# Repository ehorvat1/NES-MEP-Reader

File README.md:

# NES-MEP-Reader
Now based on amsreader-firmware Rev, 2.2.17. (from 5th Mai 2023)

So it features: WebUI with new design. WebUI componenst are now selectable in config page. WebUI works also offline (in AP mode) now. Fixed cost / kWh .Last Month info. 

From my side:
- Rel. 2.2: Fallback to Wifi AP can make AP button obsolete. 1hour plot. Additional Meter Info on status page.
- Rel. 2.3: Data fetch from meter and Web Interface now on 2 second base. New 5 minute plot.
- Rel. 2.4: Frequency Indicator, Power Factors and Reactive Data including their MQTT Topics (for Raw MQTT and HomeAssistant)
- Rel. 2.5: Added a fixed price per kWh for export.
            User can enter now a "last" counter value and a text comment for this value - idea is to enter here the last kWh from the last energy bill. A price is calculated from this "last" counter to the actual kWh counter to get an idea of costs since last energy bill. More info on minute & hour plot. Version is shown now in Status page.
- Rel. 2.6: MQTT works now for "HomeAssistant" payload. Only check for 25 Data points from BT28 (was 54)
- **current repo. state: pre 2.7: Fix table read BT23 for Gen4 meters....thanks to makerspace-reinach.ch .**
  
  **Fixed clearing of MEP error indication in header line. Fixed communication recovery and debug message if zero bytes are received.**
  
  **12 Aprl 2024, Fixed reading from table BT23 resulting in wrong "Export Reactive Arh L1L2L3"....thanks to Hubert**

  **24 Mai 2024, Only as compiled firmware in ESP32-binaries section: A version on "steroids" reading MEP port every second. Short tests did show no problems, but (as for whole project): use at own risk**

**Please Note: For MQTT I could only test payloads "raw (2 Sek.)", "raw (10 Sek.)" and "HomeAssistant" .**

This code is designed to decode data from NES (Networked Energy Services) electric smart meters which are installed in some countries in Europe (eg. Denmark and Austria, Switzerland).  
The data is presented in a graphical web interface and can also send the data to a MQTT broker which makes it suitable for home automation project.

This project is basically merging 2 other project into one:
1) amsreader-firmware (old name: AmsToMqttBridge) Rev, 2.2.17  which can found here: https://github.com/UtilitechAS/amsreader-firmware  and
2) OSGP Alliance Documentation for MEP (Multipurpose Expansion Ports) at https://github.com/OSGP-Alliance-MEP-and-Optical and the coding work from Graves Kilsgaard and Gert Lynge from www.dabbler.dk, in combination with help from NES and OSGP Alliance. See also : https://github.com/DabblerDK/MEP-SW-ESP32 

The data from NES (Echelon) smart meters is derived using the smart meters MEP (Multipurpose Expansion Port) which is using a bi-directional serial communication link. The communication is individually secured by a secret key called "MEP Basic Key" which the relevant electrical supply company (the one which own the smart meters) has to release to the customer. (In Austria this is supported by law.)

## Quick start:
1) Flash the ESP32 using files in [ESP32-binaries](https://github.com/ehorvat1/NES-MEP-Reader/tree/main/ESP32-binaries) folder and according instructions of its readme.md file. Later subsequent firmware changes can be done via Web interface by uploading a single firmware file. (Or by connecting ESP32 to a serial port which can also upload firmware.)
2) Connect to ESP32 "AP" WIFI web page. Initially the ESP32 starts in AP mode (= presenting an WIFI Access point named stromzaehler-abcd"). Connect your Laptop/Tablet to this Wifi network using **password: nesmep_esp32#V20** and open ESP32 web page which is by default on IP: 192.168.4.1

The AP SSID and password are also shown on serial connected terminal right after booting ESP32.

3) Press "NEXT" button on initial web page, and then on next page enter your Wifi SSID, credentials and optionally a hostname. Save&Reboot.
4) Connect to ESP32 web page.
ESP32 should have connected to your Wifi and should be accessable by IP but also via its Hostname (Check out your Wifi router setup page for IP address.)
5) Configuation. Open the Configuration web page (gear icon in header). Enter data to: "Price region, currency, fixed price. Set Power saving to Off, unceck Multipliers. Set up User interface to your needs.
6) Still on Configuration page: Make sure that "Meter is encrypted" checkbox is selected. Then enter the MEP Basic key in hex format. It should look similar like this: 58747A3B7E2C685656794F45404B79724F69562B .Enter/paste the 40 character long MEP basic key into the field below. You you have to get the MBK from your local energy supplyer first. Best practice is to copy/paste from an editor. After pasting the 40 char long hex key 2 trailing zeros are shown....thats fine.
7) Still on Configuration page: Set values to fields AP button = 26 (for IO26 the GPIO pin where the AP button is connected to be able to reset ESP32 to initial AP mode)."LED" = 2 (works for my ESP32 Wemos D1 Module). 
Attention: 26 is now the default which is used after each boot of ESP32. 
The serial port connection to the MEP port is fixed in the code to UART2 which is using IO16 & IO17. RTS (Request to send) is coded to IO05.
8) For MQTT setup: Enter a MQTTs broker IP into field "Host", a unique name to "Client ID" (unique for the MQTT broker) e.g. SM1 and enter a MQTT topic into "Publish topic" field. This will be the base topic name. e.g. smartmeter.
9) 

## Wifi function (STA mode or AP mode):
The option on configuration page in section Wifi called:  "Start a Wifi AP on home Wifi connection problem" will enable this:
If the configured Wifi (should be your home Wifi) can not be reached within app. 2 minutes the ESP32 will swap to Wifi AP mode and will present a AP named "Stromzaehler-abcd" with password mentioned in above pt. 2. 

Software will try to re-connect to the configured Wifi if no client is connected to this AP for 90 seconds. So if one is connected to AP Wifi the device will stay in AP mode. Please mind that most devices will do a automatic reconnect to the AP Wifi if the Wifi connection "Stromzaehler-abcd" was once used. This could prevent the ESP32 from automatically reconnecting to defined STA Wifi.

"AP" button still is an option to swap between configured WLAN and an Wifi Access point called "Stromzaehler-abcd". The AP button must be pressed longer than 5 seconds to swap Wifi mode.

## Hardware:
For hardware please check repository [Hardware](https://github.com/ehorvat1/NES-MEP-Reader/tree/main/Hardware) and also the development done by Dabbler group at www.dabbler.dk

## Notes:
1) This was tested only on NES Smart Meters Type: 83332-3I and 83334-3I 
2) There might be problems with power supply from NES Smart meter. It seems that some meters do not supply sufficient power to ESP32. As a result you might see frequent crashes or the serial communication to MEP port not working at all. If this happens remove the DCDC converter (!) and power the ESP32 module directly from USB.
3) NES (Networked Energy Services) smart meters were previously manufactured and sold with the "Echelon" brand name.
4) Currently only ESP32 is supported although you may find remainders of ESP8266 in the code. (Yes I want to make it ESP8266 compatible....)
5) MBK (MEP Basic Key) must be entered in its "hex" representation. This is a 40 char long string like this: 58747A3B7E2C685656794F45404B79724F69562B . You might receive a MEP Basic key in ascii format (just 20 char.) which has to be converted to hex manually - each single ASCII character gives a 2 digit hex number.
6) I have done some translations to German on the main web interface. A english version will follow.
7) Following raw MQTT topics should work in MQTT raw mode - they are published on a pure time basis even if they do not change the value.:
     - Publish topic + "/meter/mep_data_ready"
     - Publish topic + "/meter/mep_alivecounter"
     - Publish topic + "/meter/manufacturer"
     - Publish topic + "/meter/model"
     - Publish topic + "/meter/serialnumber"
     - Publish topic + "/meter/firmwareversion"
     - Publish topic + "/meter/hardwareversion"
     - Publish topic + "/meter/clock"
     - Publish topic + "/meter/import/active"
     - Publish topic + "/meter/import/active/accumulated"
     - Publish topic + "/meter/export/active"
     - Publish topic + "/meter/export/active/accumulated"
     - Publish topic + "/meter/import/reactive"
     - Publish topic + "/meter/export/reactive"     
     - Publish topic + "/meter/import/reactive/accumulated"
     - Publish topic + "/meter/export/reactive/accumulated"
     - Publish topic + "/meter/l1/voltage"
     - Publish topic + "/meter/l2/voltage"
     - Publish topic + "/meter/l3/voltage"
     - Publish topic + "/meter/l1/current"
     - Publish topic + "/meter/l2/current"
     - Publish topic + "/meter/l3/current"
     - Publish topic + "/meter/l1/powerfactor"
     - Publish topic + "/meter/l2/powerfactor"
     - Publish topic + "/meter/l3/powerfactor"
     - Publish topic + "/meter/appowerVA"
     - Publish topic + "/meter/frequency"
     - Publish topic + "/meter/reactivepower_Q1"
     - Publish topic + "/meter/reactivepower_Q2"
     - Publish topic + "/meter/reactivepower_Q3"
     - Publish topic + "/meter/reactivepower_Q4"
     - Publish topic + "/realtime/import/hour"
     - Publish topic + "/realtime/import/day"
     - Publish topic + "/realtime/import/month"
     - Publish topic + "/realtime/export/hour"
     - Publish topic + "/realtime/export/day"
     - Publish topic + "/realtime/export/month"
     - Publish topic + "/realtime/import/cost_kwh"
	 
     - Publish topic + "/realtime/import/last_counter_value"
     - Publish topic + "/realtime/import/last_counter_info"
     - Publish topic + "/realtime/import/last_counter_diff"
     - Publish topic + "/realtime/import/last_counter_costs"
     - Publish topic + "/realtime/export/refund_kwh"
     - Publish topic + "/realtime/export/last_counter_value"
     - Publish topic + "/realtime/export/last_counter_info"
     - Publish topic + "/realtime/export/last_counter_diff"
     - Publish topic + "/realtime/export/last_counter_refund"

So for example, if you set the "Publish topic" in MQTT configuration to "smartmeter" the actual power used is published with full topic: smartmeter/meter/import/active   (Topics are case sensitive !)

8) MQTT for HomeAssistant: HA creates/discovers nummerical data as "Sensors". Exceptions is String data which has to be extracted from JSON data manually.

## Web interface:
The web interface is very similar to original "amsreader-firmware". I have added a 60 Minute plot, and translated to German language.
The help icons on the configuration page are linked to original "amsreader-firmware" site. Serial Port and RTS Pin are described also on config page.

## Building this project with PlatformIO
To build this project, you need [PlatformIO](https://platformio.org/) installed.

It is recommended to use Visual Studio Code with the PlatformIO plugin for development.

[Visual Studio Code](https://code.visualstudio.com/download)

[PlatformIO vscode plugin](https://platformio.org/install/ide?install=vscode)

For development purposes, copy the ```platformio-user.ini-example``` to ```platformio-user.ini``` and customize to your preference. The code will adapt to the platform and board set in your profile.

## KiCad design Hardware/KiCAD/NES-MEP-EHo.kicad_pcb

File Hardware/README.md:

# Hardware 
Updated Rev2 uploaded 21.Dec 2022

## Used parts:
1) A DC/DC step down converter set to 3.3 Volt (source: https://www.az-delivery.de/en/collections/stromversorgung/products/lm2596s-dc-dc-step-down-modul-1 )
2) A ESP32 D1 Mini Module (source: https://www.az-delivery.de/en/collections/esp32/products/esp32-d1-mini)
3) A "selfmade" printed cirquit board based on attached KICAD project. [Schema in pdf format](https://github.com/ehorvat1/NES-MEP-Reader/blob/main/Hardware/NES-MEP-EHo-shema-Rev2.pdf)

### Issues:
There might be problems with power supply from NES Smart meter. It seems that some meters do not supply sufficient power to ESP32. Or the MAX3232 charge pumps interfering with the step down converter. As a result you might see frequent crashes or the serial communication to MEP port not working. You might also notice that the MAX3232 and the step down converter getting quite warm. 
If this happens try:
1) Try with a (oversized) 470uF or 1000uF capacitor on the +3.3V and GND. This helped a lot, but still 2 or 3 tries to connect may be needed.
2) Always helps: Remove the DCDC converter (!) and power the ESP32 module directly from USB.

### Notes:
1) I have used a small "connector" board to connect to the MEP port and a flat ribbon cable. In this way the signals are transported outside of the meter. The flat ribbon cable fits through the open gap where the meter is mounted into the electric cabinet. This all is done because here in my place the MEP port is not accesable, it is covered by a plastic cover which is sealed off by the power supply company. Check out a photo of the cable and small connector card here: https://github.com/ehorvat1/NES-MEP-Reader/blob/main/Hardware/Pictures-Rev1/Assembly.JPG
2) The spacing of the MEP port terminals is different between NES smart meter models. Therefore just 5 short wires are connected to the "connector" board.

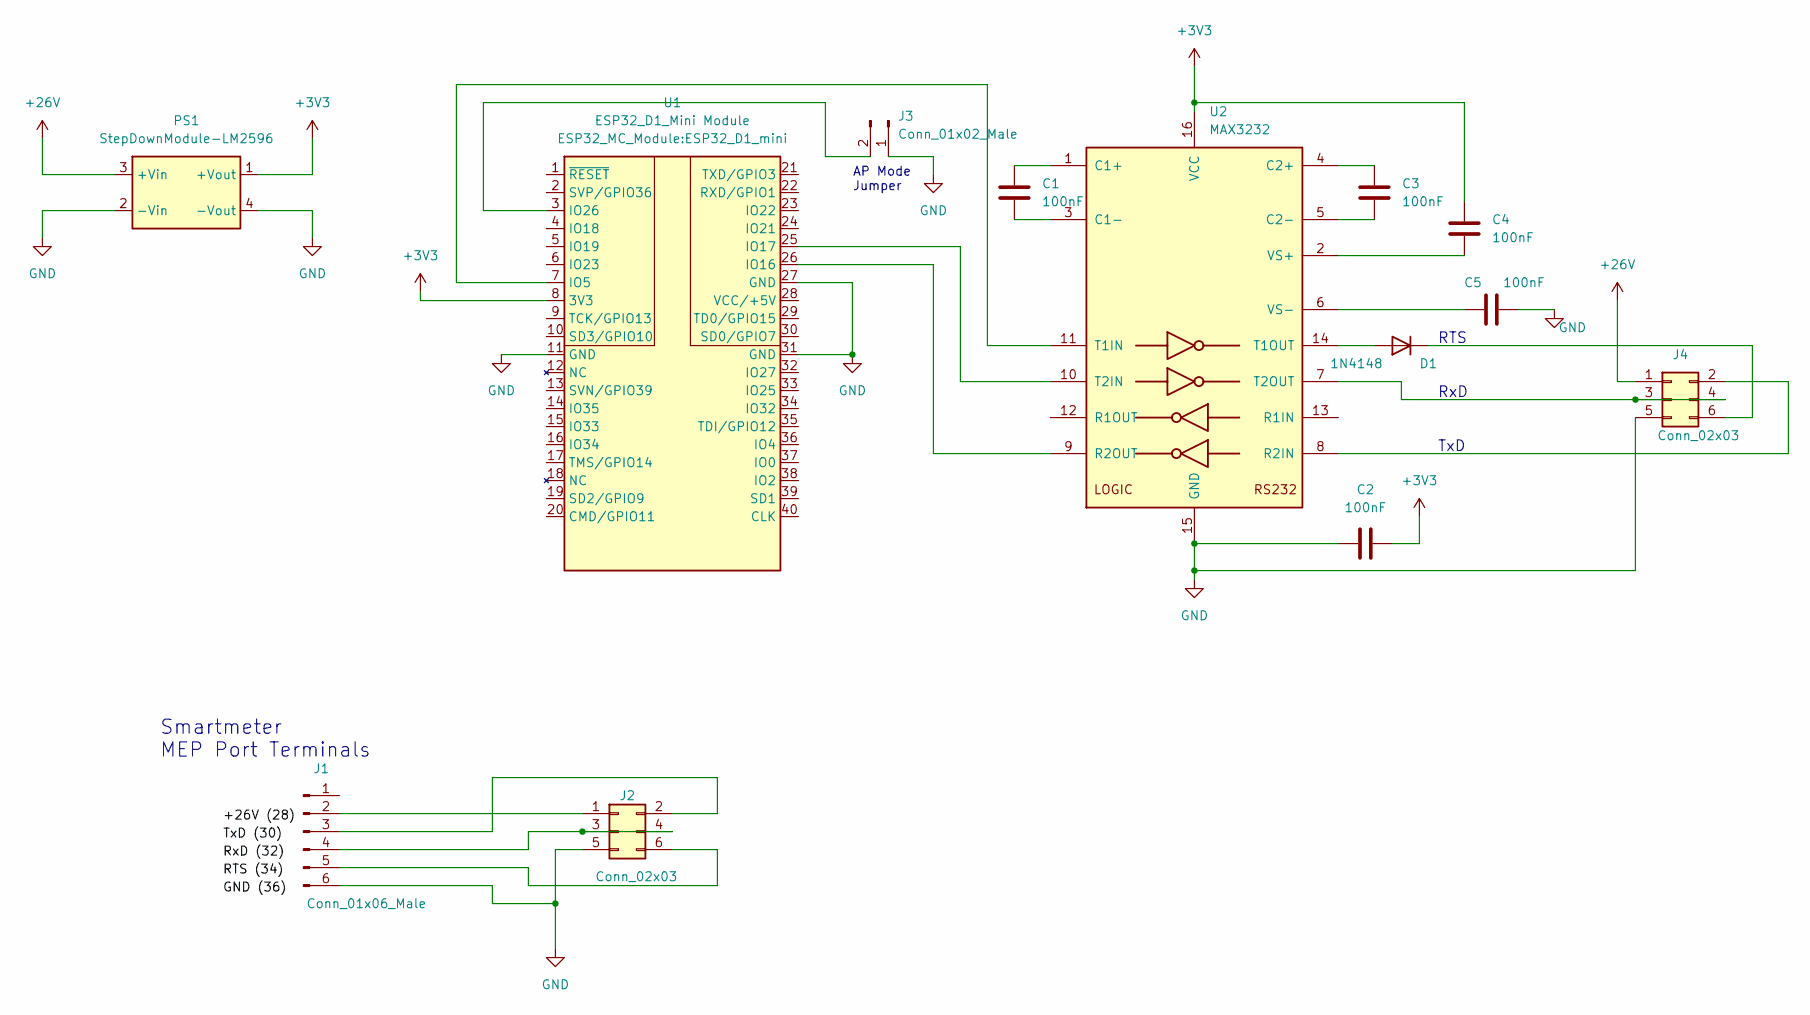
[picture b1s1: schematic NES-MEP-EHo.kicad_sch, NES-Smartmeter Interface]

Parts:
C1, C2, C3, C4, C5: 100nF; C_Rect_L7.0mm_W3.5mm_P5.00mm
D1: 1N4148; D_DO-35_SOD27_P7.62mm_Horizontal
J1: Conn_01x06_Male; SolderWire-1sqmm_1x06_P5.4mm_D1.4mm_OD2.7mm
J2, J4: Conn_02x03; IDC-Header_2x03_P2.54mm_Vertical
J3: Conn_01x02_Male; PinHeader_1x02_P2.54mm_Vertical
PS1: StepDownModule-LM2596; DCDC-StepDown-LM2596-THT
U1: ESP32_D1_Mini Module; ESP32_D1_mini
U2: MAX3232; DIP-16_W7.62mm_Socket

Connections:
+3V3: C2.2, C4.1, PS1.1 (+Vout), U1.8 (3V3), U2.16 (VCC)
+26V: J4.1, PS1.3 (+Vin)
GND: C2.1, C5.1, J1.6, J2.5, J3.1, J4.5, PS1.2 (-Vin), PS1.4 (-Vout), U1.11 (GND), U1.27 (GND), U1.31 (GND), U2.15 (GND)
unnamed: C1.1, U2.1 (C1+)
unnamed: C1.2, U2.3 (C1-)
unnamed: C3.1, U2.4 (C2+)
unnamed: C3.2, U2.5 (C2-)
unnamed: C4.2, U2.2 (VS+)
unnamed: C5.2, U2.6 (VS-)
unnamed: D1.1 (K), J4.6
unnamed: D1.2 (A), U2.14 (T1OUT)
unnamed: J1.2, J2.1
unnamed: J1.3, J2.2
unnamed: J1.4, J2.3, J2.4
unnamed: J1.5, J2.6
unnamed: J3.2, U1.3 (IO26)
unnamed: J4.2, U2.8 (R2IN)
unnamed: J4.3, J4.4, U2.7 (T2OUT)
unnamed: U1.7 (IO5), U2.11 (T1IN)
unnamed: U1.25 (IO17), U2.10 (T2IN)
unnamed: U1.26 (IO16), U2.9 (R2OUT)

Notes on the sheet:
RTS
TxD
Smartmeter MEP Port Terminals
AP Mode Jumper
RxD

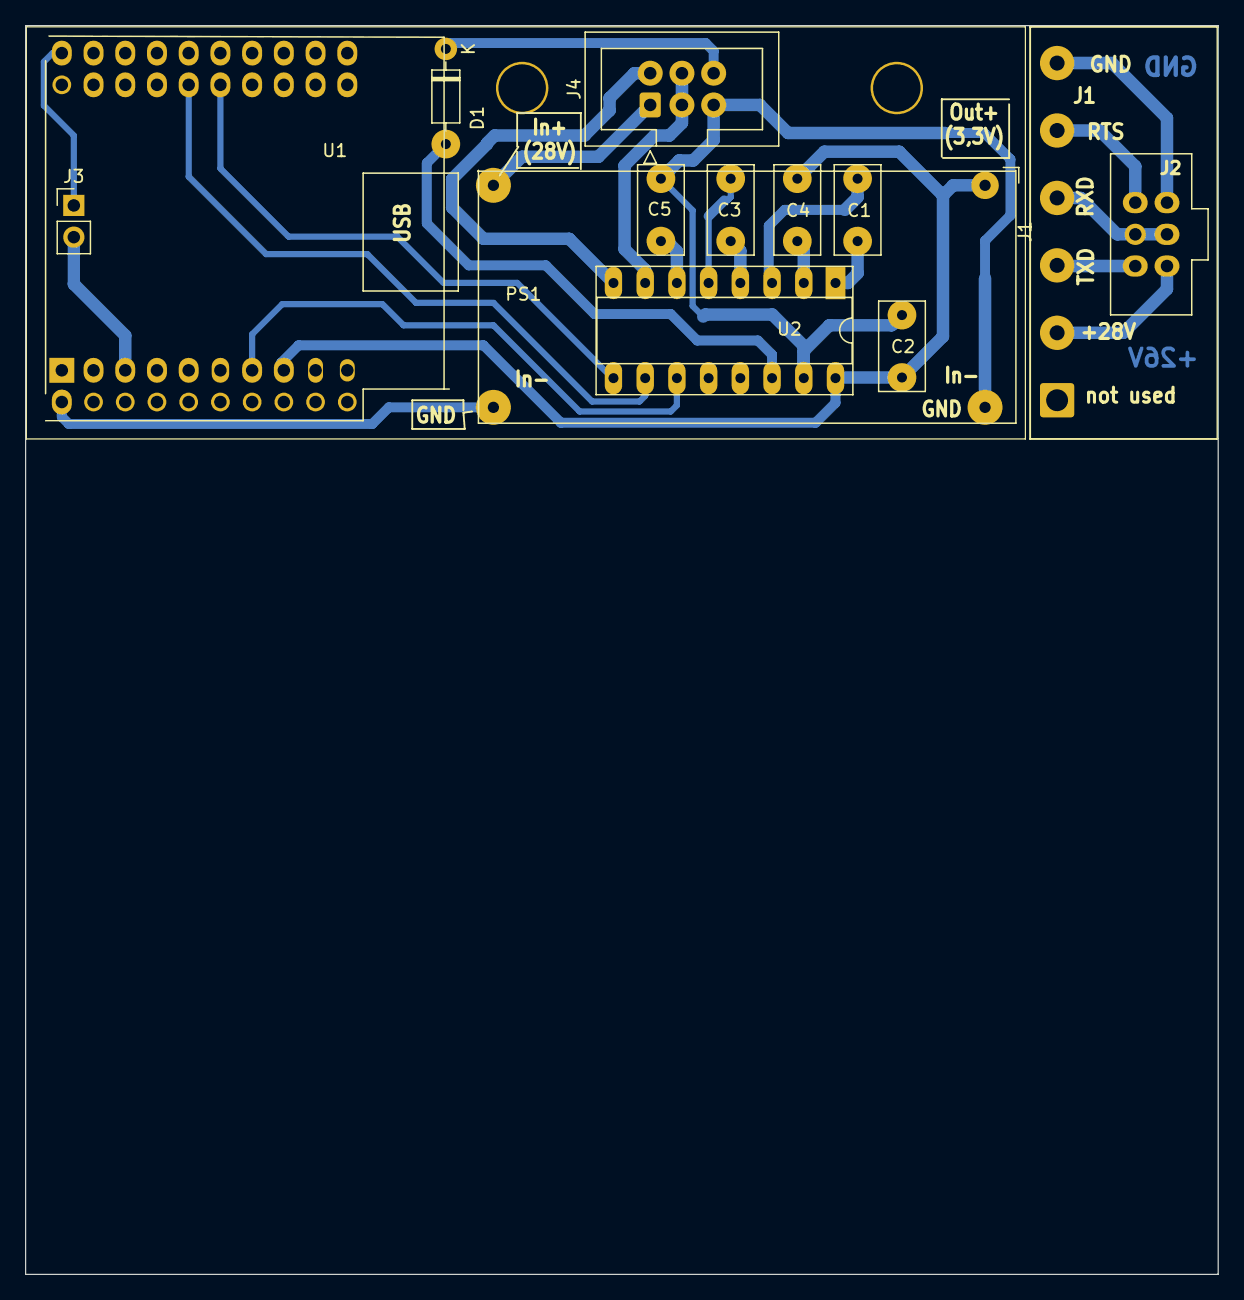
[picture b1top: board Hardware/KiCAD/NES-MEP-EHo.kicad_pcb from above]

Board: 2 copper layers, 95.5 x 100.0 mm, 13 parts (0 on the bottom side), 21 nets.

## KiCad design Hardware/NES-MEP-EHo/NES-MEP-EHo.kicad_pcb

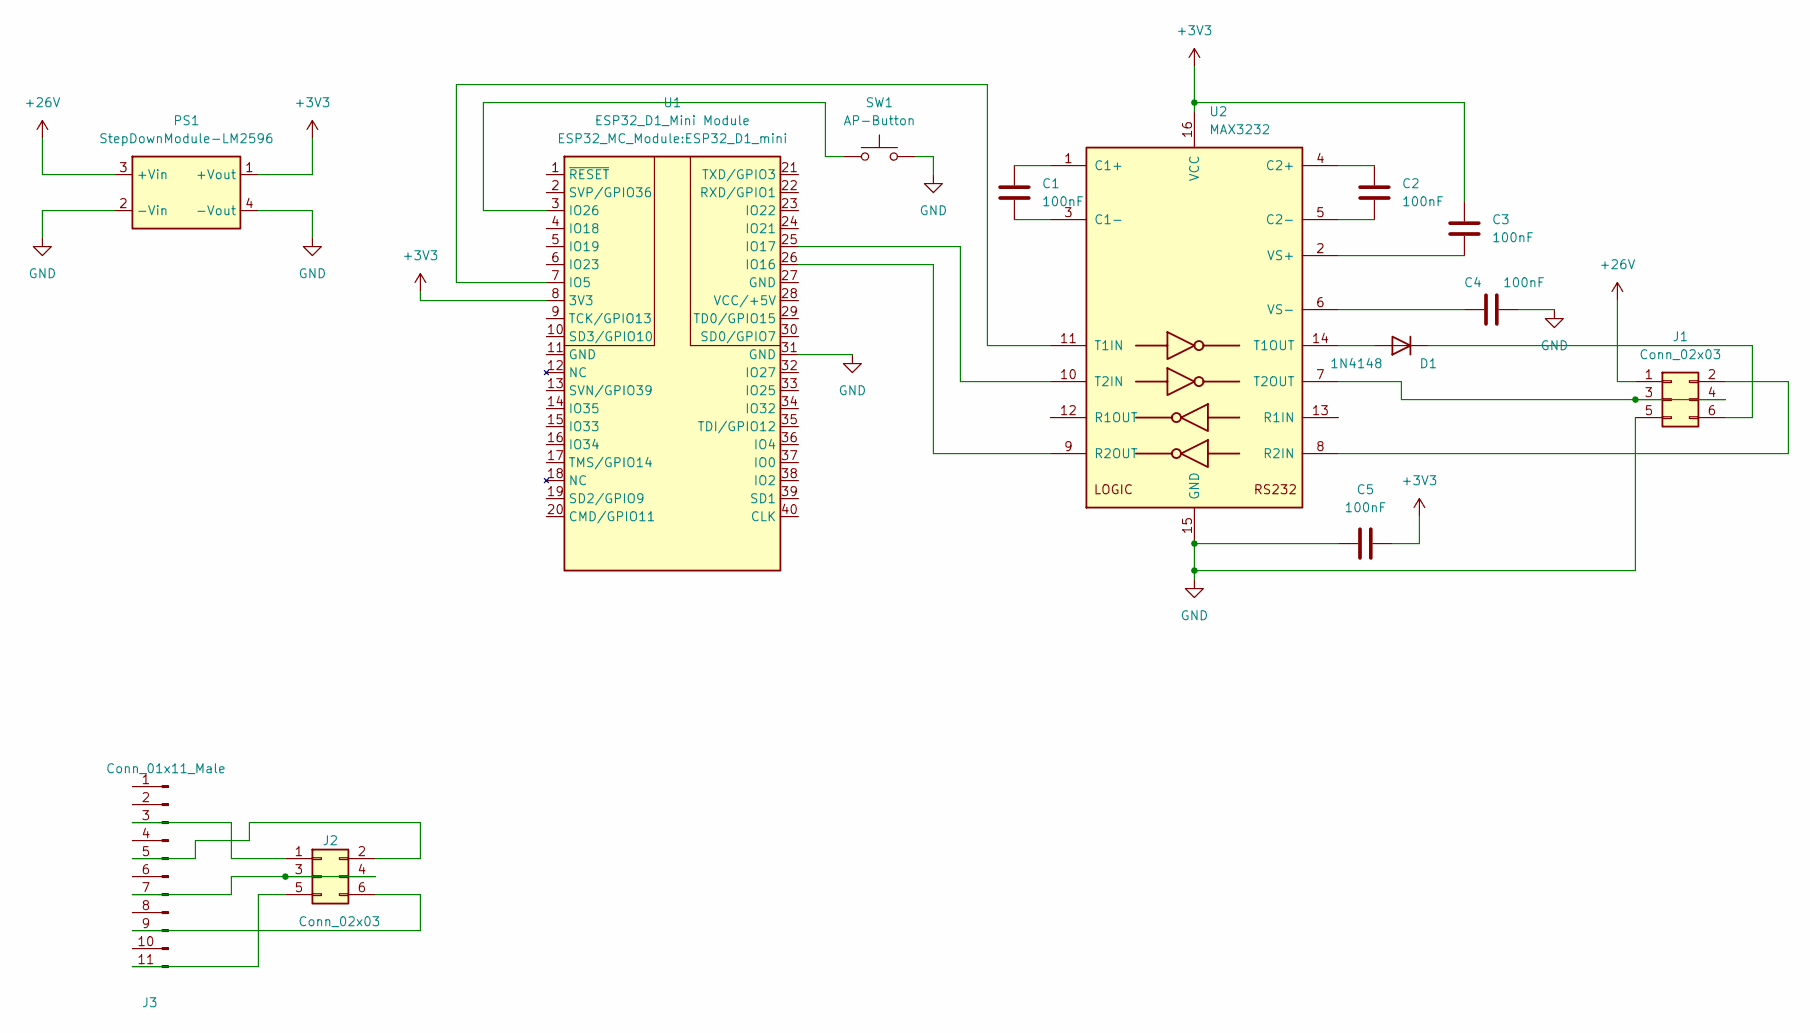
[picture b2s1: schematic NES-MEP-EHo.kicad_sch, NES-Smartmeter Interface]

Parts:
C1, C2, C3, C4, C5: 100nF; C_Rect_L7.0mm_W3.5mm_P5.00mm
D1: 1N4148; D_DO-35_SOD27_P7.62mm_Horizontal
J1, J2: Conn_02x03; IDC-Header_2x03_P2.54mm_Vertical
J3: Conn_01x11_Male; PinSocket_1x11_P2.54mm_Vertical
PS1: StepDownModule-LM2596; DCDC-StepDown-LM2596-THT
SW1: AP-Button; SW_PUSH_6mm
U1: ESP32_D1_Mini Module; ESP32_D1_mini
U2: MAX3232; DIP-16_W7.62mm_Socket

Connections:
+3V3: C3.1, C5.2, PS1.1 (+Vout), U1.8 (3V3), U2.16 (VCC)
+26V: J1.1, PS1.3 (+Vin)
GND: C4.1, C5.1, J1.5, PS1.2 (-Vin), PS1.4 (-Vout), SW1.2, U1.31 (GND), U2.15 (GND)
unnamed: C1.1, U2.1 (C1+)
unnamed: C1.2, U2.3 (C1-)
unnamed: C2.1, U2.4 (C2+)
unnamed: C2.2, U2.5 (C2-)
unnamed: C3.2, U2.2 (VS+)
unnamed: C4.2, U2.6 (VS-)
unnamed: D1.1 (K), J1.6
unnamed: D1.2 (A), U2.14 (T1OUT)
unnamed: J1.2, U2.8 (R2IN)
unnamed: J1.3, J1.4, U2.7 (T2OUT)
unnamed: J2.1, J3.3
unnamed: J2.2, J3.5
unnamed: J2.3, J2.4, J3.7
unnamed: J2.5, J3.11
unnamed: J2.6, J3.9
unnamed: SW1.1, U1.3 (IO26)
unnamed: U1.7 (IO5), U2.11 (T1IN)
unnamed: U1.25 (IO17), U2.10 (T2IN)
unnamed: U1.26 (IO16), U2.9 (R2OUT)

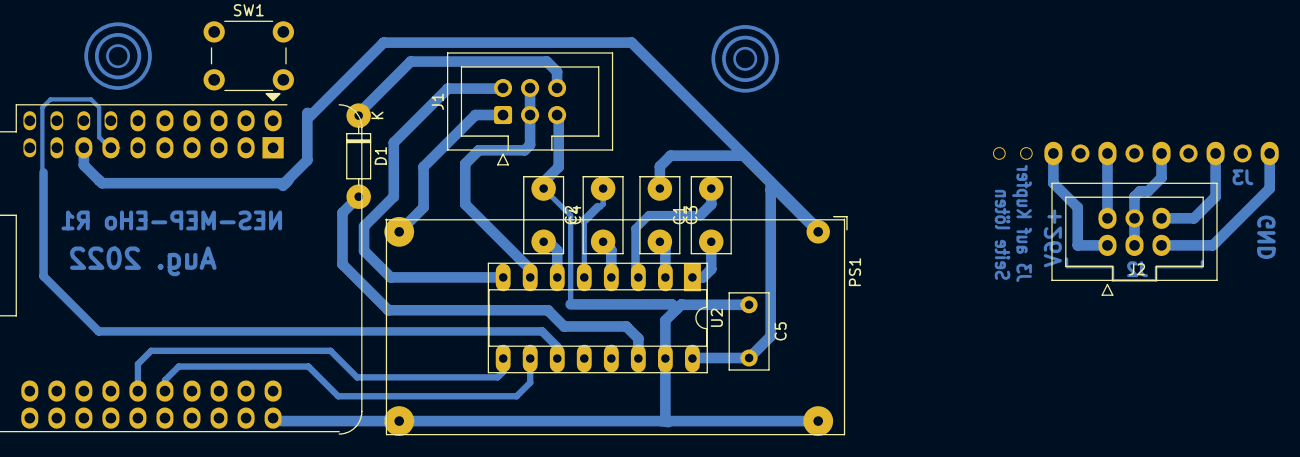
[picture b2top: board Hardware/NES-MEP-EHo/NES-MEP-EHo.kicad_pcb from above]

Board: 2 copper layers, 13 parts (1 on the bottom side), 22 nets.

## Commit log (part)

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2022-12-21 Create Rev1
2023-09-12 Add files via upload
    Just read in first 25 values from BT28 (original was 54*4)
2023-09-12 Add files via upload
    New (prelim) Revision 2.6 Number and Date
2023-11-19 Add files via upload
    Fix table read BT23 for Gen4 meters....thanks to makerspace-reinach.ch
2023-11-19 Add files via upload
    Updated Version to show to pre 2.7 and Date to 19.Nov2023
2023-12-04 Clearing of MEP Error indication on header fixed.
2023-12-04 New date for version indicator
2023-12-04 Fixed clearing of MEP error indicator in header
2023-12-07 Fixed error recovery and debugging message in case zero bytes are received
2023-12-07 Due to fixes, show new release date "7. Dez 2023"
2023-12-11 Add CHF also to last counter values, cleanup on config page.
2023-12-11 Add CHF to last Values, cleanup on config page.
2024-04-02 Fixed issue with "Accumulated reactive export "
    Fixed issue with "Accumulated reactive export " reading from BT23 index 3.
    Now requesting 16 bytes from table BT23 (instead of 13)
2024-04-02 Updated build date in Status page
2024-04-18 Test Firmware für Hubert
2024-04-18 BT21 read fixed (3rd attemt)
2024-05-24 app. 1 Second read rate
    Faster MEP Port read rate ... now 1 second (in real world test ca. 1050 to 1250 ms). Also faster on MQTT, web server/page updates. 5 Minute Plot changed to 2.5 Minute plot.
2024-05-24 Changed MEP Port read rate , now 1 second (was 2)
    Faster MEP Port read rate ... now 1 second (in real world test ca. 1050 to 1150 ms). Also faster on MQTT, web server/page updates. 5 Minute Plot changed to 2.5 Minute plot.
2024-05-24 Changed MEP Port read rate now 1 second (was 2)
    Faster MEP Port read rate ... now 1 second (in real world test ca. 980 to 1150 ms). Also faster on MQTT, web server/page updates. 5 Minute Plot changed to 2.5 Minute plot.
